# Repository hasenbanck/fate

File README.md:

# Fate

Fate is a annutation adapter to connect an electrostatic amplifier with a ADC for audio measurments.

It steps down the voltage from maximal 1.6 kVpp down to 40 Vpp. It also contains some diodes for
overvoltage protection (use low capacitance diodes).

## Simulation

[CircuitJS](https://www.falstad.com/circuit/circuitjs.html?cct=$+13+0.0000014204545454545454+0.15814360605671443+53+5+43%0AR+-32+64+-64+64+0+1+22000+400+0+0+0.5%0AR+-32+288+-64+288+0+1+22000+400+0+3.141592653589793+0.5%0Ap+-32+64+-32+288+1+0%0Ar+80+288+32+288+0+35000%0Aw+96+64+80+64+0%0Aw+96+288+80+288+0%0Ap+288+64+288+288+1+0%0Ar+96+256+96+208+0+1800%0Aw+-32+64+-16+64+0%0Aw+-32+288+-16+288+0%0Aw+160+64+96+64+0%0Ar+384+208+384+144+0+100000%0Aw+384+64+384+144+0%0Aw+384+288+384+208+0%0Ar+-16+288+32+288+0+35000%0Ar+-16+64+32+64+0+35000%0Ar+80+64+32+64+0+35000%0Ar+96+144+96+96+0+1800%0Aw+96+288+160+288+0%0Aw+96+96+96+64+0%0Aw+96+256+96+288+0%0Aw+288+64+384+64+0%0Aw+288+288+384+288+0%0Aw+96+144+96+208+0%0A34+fwdrop%5Cq0.37+0+1.0000000000000001e-7+0+0.887514607756+20%0Ad+160+128+160+176+2+fwdrop%5Cq0.37%0Aw+160+64+208+64+0%0Aw+160+288+208+288+0%0Ac+208+144+208+208+0+5e-11+3.331173440527873%0Aw+208+64+288+64+0%0Aw+208+288+288+288+0%0Aw+160+64+160+128+0%0Aw+160+224+160+288+0%0Aw+208+64+208+144+0%0Aw+208+208+208+288+0%0Ad+160+224+160+176+2+fwdrop%5Cq0.37%0Ax+122+306+303+309+4+12+(capacitor%5Csonly%5Csfor%5Cssimulation)%0Ag+96+176+64+176+0%0Ao+2+1+0+12546+800+0.0001+0+1%0Ao+6+1+0+12546+19.373898404904125+0.0001+1+1%0A)

## License
CERN Open Hardware License 1.2

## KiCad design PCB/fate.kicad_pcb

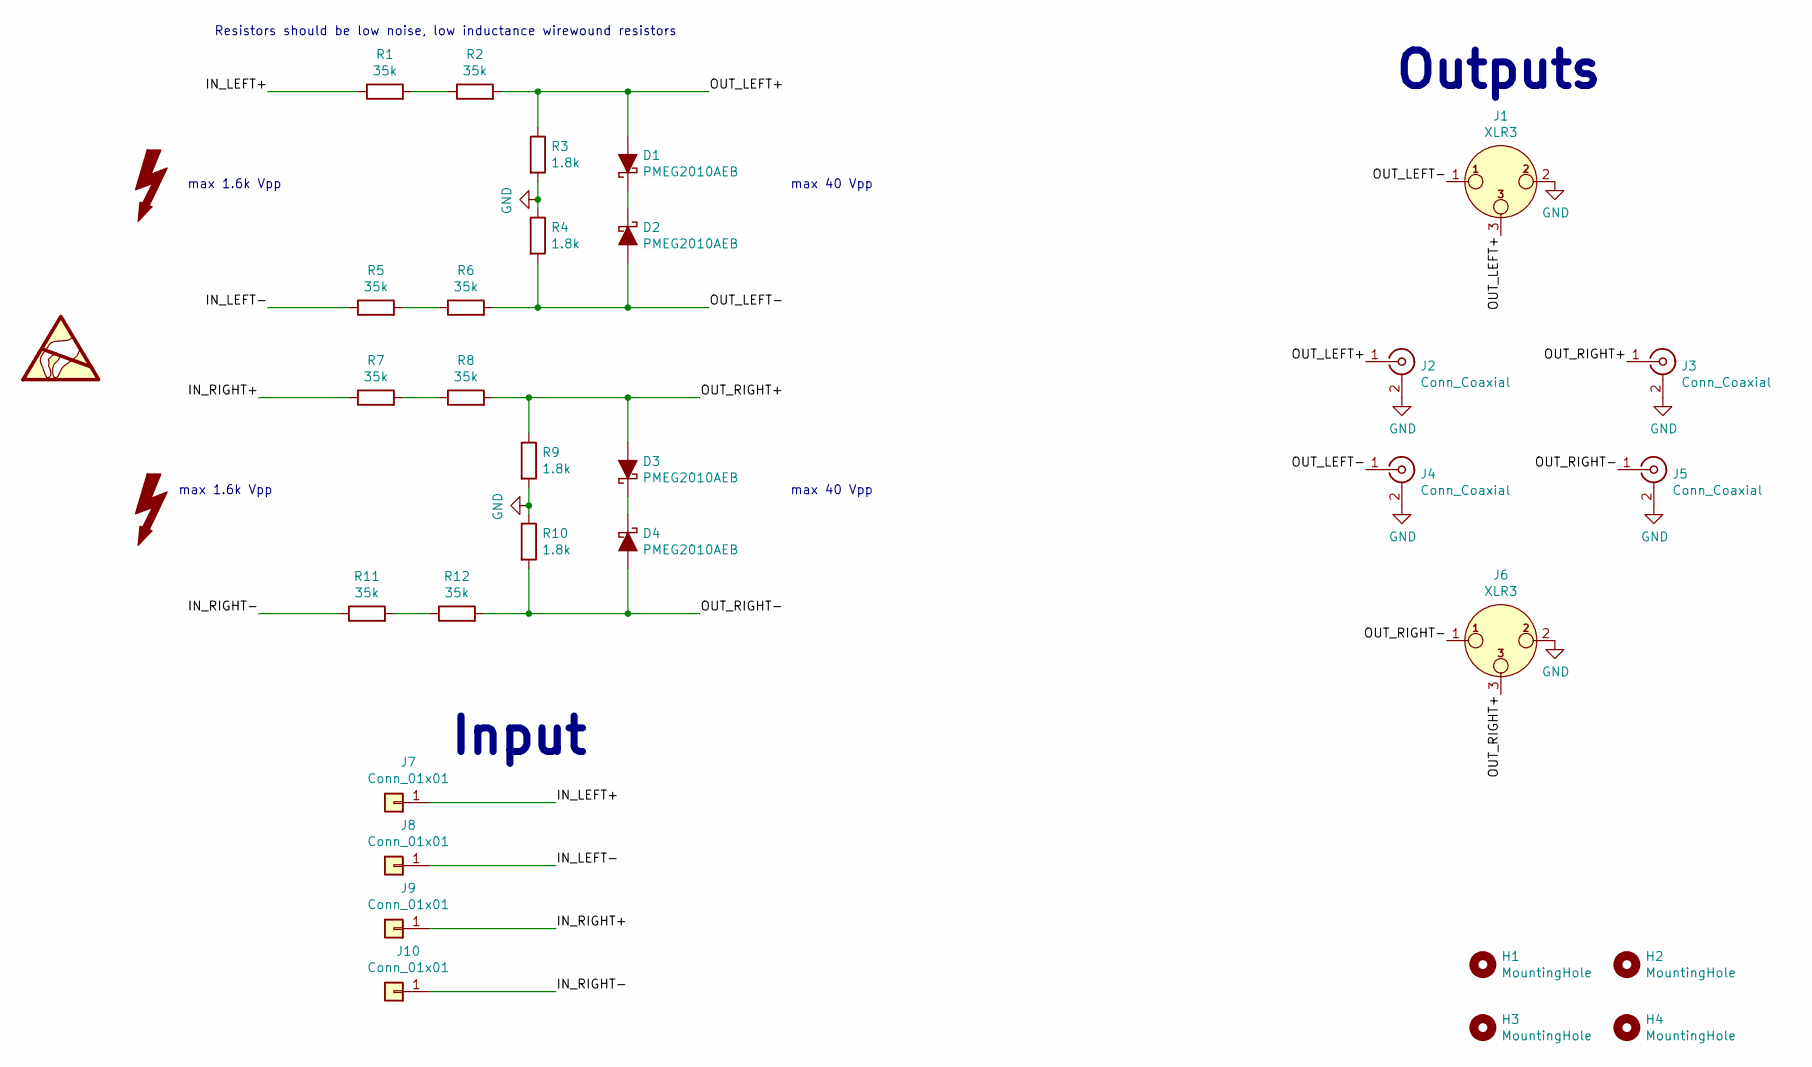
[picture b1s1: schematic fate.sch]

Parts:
D1, D2, D3, D4: PMEG2010AEB; D_SOD-523
H1, H2, H3, H4: MountingHole; MountingHole_3.2mm_M3_Pad
J1, J6: XLR3; XLR-NC3MA
J2, J3, J4, J5: Conn_Coaxial; CUI_RCJ-017
J7, J8, J9, J10: Conn_01x01; SolderWirePad_1x01_Drill2mm
R1, R2, R5, R6, R7, R8, R11, R12: 35k; R_Axial_Power_L25.0mm_W9.0mm_P30.48mm
R3, R4, R9, R10: 1.8k; R_Axial_DIN0516_L15.5mm_D5.0mm_P25.40mm_Horizontal
SYM1: SYM_ESD_Large; OSHW-Logo2_24.3x20mm_SilkScreen
SYM2, SYM3: SYM_Flash_Large; Symbol_HighVoltage_Type1_CopperTop_Big

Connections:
/IN_LEFT+: J7.1, R1.1
/IN_LEFT-: J8.1, R5.1
/IN_RIGHT+: J9.1, R7.1
/IN_RIGHT-: J10.1, R11.1
/OUT_LEFT+: D1.2 (A), J1.3, J2.1 (In), R2.2, R3.1
/OUT_LEFT-: D2.2 (A), J1.1, J4.1 (In), R4.2, R6.2
/OUT_RIGHT+: D3.2 (A), J3.1 (In), J6.3, R8.2, R9.1
/OUT_RIGHT-: D4.2 (A), J5.1 (In), J6.1, R10.2, R12.2
GND: J1.2, J2.2 (Ext), J3.2 (Ext), J4.2 (Ext), J5.2 (Ext), J6.2, R3.2, R4.1, R9.2, R10.1
unnamed: D1.1 (K), D2.1 (K)
unnamed: D3.1 (K), D4.1 (K)
unnamed: R1.2, R2.1
unnamed: R5.2, R6.1
unnamed: R7.2, R8.1
unnamed: R11.2, R12.1

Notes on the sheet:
Outputs
Input
max 1.6k Vpp
max 40 Vpp
Resistors should be low noise, low inductance wirewound resistors

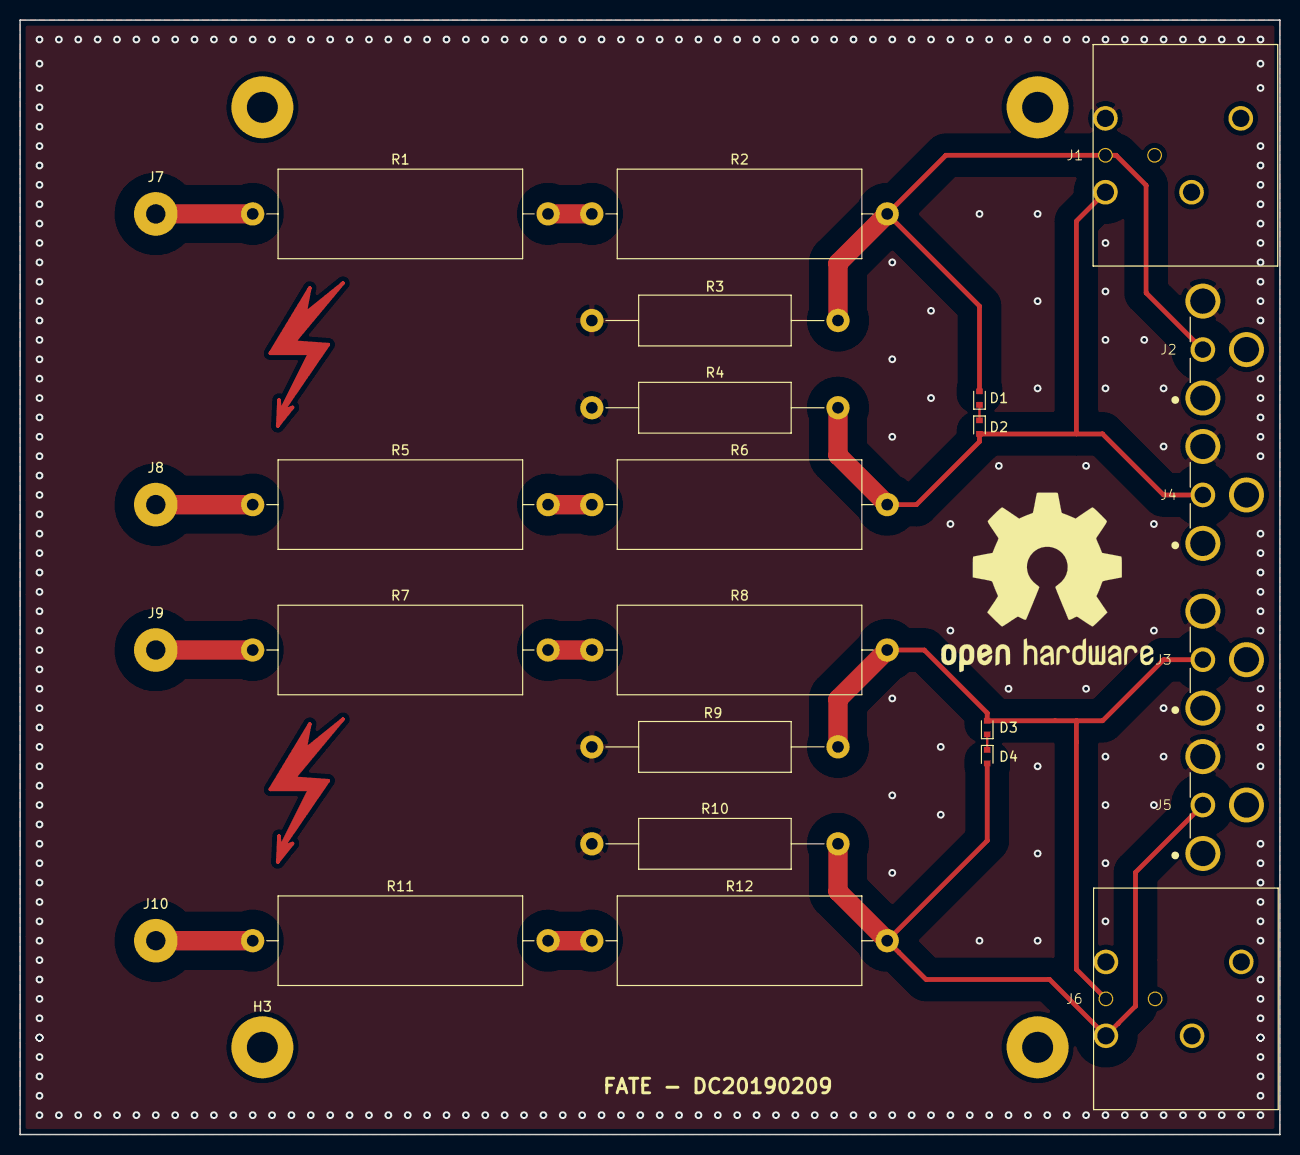
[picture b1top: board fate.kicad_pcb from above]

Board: 2 copper layers, 130.0 x 115.0 mm, 33 parts (0 on the bottom side), 15 nets.

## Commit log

2019-02-08 Update resistors to use "NS" resistors
    "NS" resistors have a special winding to be "non-inductive".
2019-02-09 Add ground reference between differential signal lines
2019-02-09 Update simulation link
